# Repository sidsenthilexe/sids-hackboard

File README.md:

# Sid's Hackboard
My hackboard is pretty closely based on my current keyboard (Steelseries Apex 3 TKL) because it fits very well for what I need it to do. Probably could have optimized it more but ran out of time.                         
I'll probably make some keys macros especially the cluster around Delete.                   
It also includes a volume knob + a switch for play/pause, skip, and rewind.                         
This was actually way easier than hackpad because I now use KiCad and Fusion a lot more (even for other projects), but figuring out how to do the integrated plate was a bit annoying, and drafting the edges also took some figuring out.                      
Anyway I made a (hopefully) functional keyboard.                    

## Key Features:
* Standard TKL layout
* Plate with integrated case
* Magnetic lift bar - totally not copied from s76
* Volume knob
* Probably way too tall but I didn't bother to measure properly

## CAD/case:
M3 (M5? idek) bolts and heatset inserts are used to hold the 2 pieces together, and an integrated plate is used to hold the pcb.

## PCB:
A matrix is wired to prevent ghosting - the wiring took way too long. There are 84 total keys and one rotary encoder + switch, organized in 17 columns and 6 rows.

## Firmware:
KMK was used for the firmware, I still need to figure out how to implement the volume controls though.

## BOM:
|ITEM|QTY|PRICE|
|----|---|-----|
|Orpheus Pico|1|price|
|mx switches|qty|price|
|stabs|qty|price|
|encoder|qty|price|
|3x10x60mm Magnets|1 pack of 4|5.99|
|1N4148 diodes|qty|price|
|keycaps|qty|price|
|bolts|qty|price|
|heatset inserts|qty|price|

## Images:
Fully assembled:          
               
Schematic:          
                           
PCB:            
                                                   
Case:

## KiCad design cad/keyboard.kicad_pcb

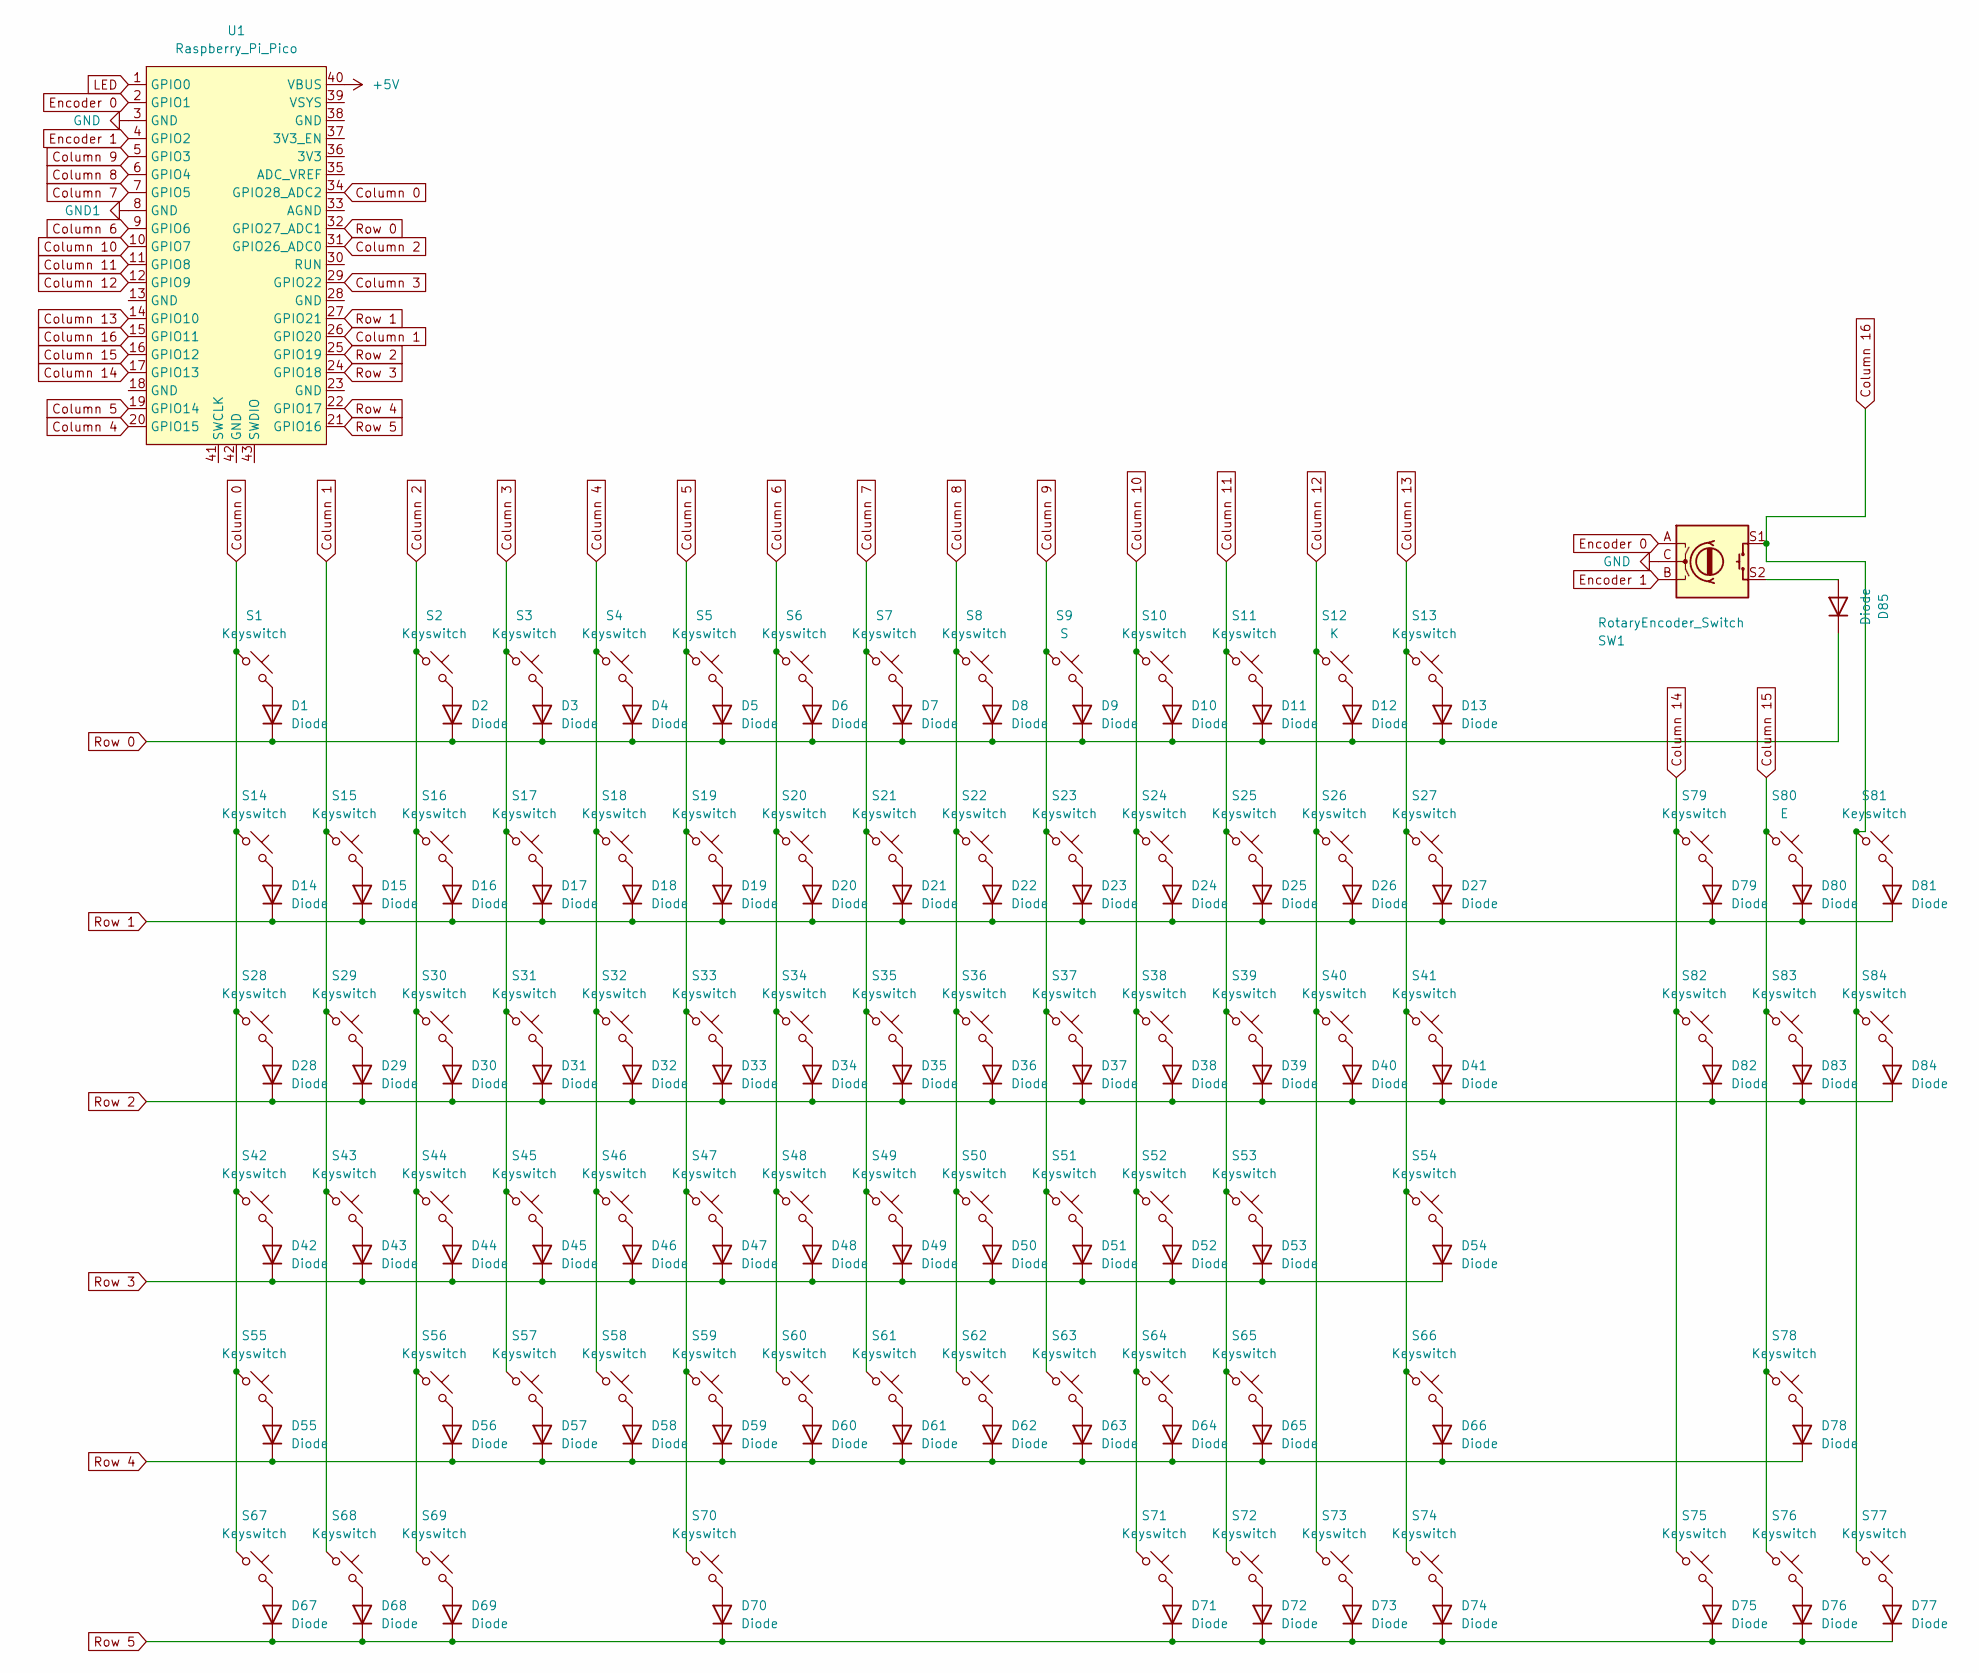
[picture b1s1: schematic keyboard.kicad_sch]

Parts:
D1, D2, D3, D4, D5, D6, D7, D8, D9, D10, D11, D12, D13, D14, D15, D16, D17, D18, D19, D20, D21, D22, D23, D24, D25, D26, D27, D28, D29, D30, D31, D32, D33, D34, D35, D36, D37, D38, D39, D40, D41, D42, D43, D44, D45, D46, D47, D48, D49, D50, D51, D52, D53, D54, D55, D56, D57, D58, D59, D60, D61, D62, D63, D64, D65, D66, D67, D68, D69, D70, D71, D72, D73, D74, D75, D76, D77, D78, D79, D80, D81, D82, D83, D84, D85: Diode; Diode_DO-35
S1, S2, S3, S4, S5, S6, S7, S8, S10, S11, S13, S14, S15, S16, S17, S18, S19, S20, S21, S22, S23, S24, S25, S26, S29, S30, S31, S32, S33, S34, S35, S36, S37, S38, S39, S40, S43, S44, S45, S46, S47, S48, S49, S50, S51, S52, S53, S56, S57, S58, S59, S60, S61, S62, S63, S64, S65, S75, S76, S77, S78, S79, S81, S82, S83, S84: Keyswitch; MX_PCB_1.00u
S9: S; MX_PCB_1.00u
S12: K; MX_PCB_1.00u
S27: Keyswitch; MX_PCB_2.00u
S28, S41: Keyswitch; MX_PCB_1.50u
S42: Keyswitch; MX_PCB_1.75u
S54, S55: Keyswitch; MX_PCB_2.25u
S66: Keyswitch; MX_PCB_2.75u
S67, S68, S69, S71, S72, S73, S74: Keyswitch; MX_PCB_1.25u
S70: Keyswitch; MX_PCB_6.25u
S80: E; MX_PCB_1.00u
SW1: RotaryEncoder_Switch; RotaryEncoder_Alps_EC11E-Switch_Vertical_H20mm
U1: Raspberry_Pi_Pico

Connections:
+5V: U1.40 (VBUS)
Column 0: S1.1, S14.1, S28.1, S42.1, S55.1, S67.1, U1.34 (GPIO28_ADC2)
Column 1: S15.1, S29.1, S43.1, S68.1, U1.26 (GPIO20)
Column 2: S2.1, S16.1, S30.1, S44.1, S56.1, S69.1, U1.31 (GPIO26_ADC0)
Column 3: S3.1, S17.1, S31.1, S45.1, S57.1, U1.29 (GPIO22)
Column 4: S4.1, S18.1, S32.1, S46.1, S58.1, U1.20 (GPIO15)
Column 5: S5.1, S19.1, S33.1, S47.1, S59.1, S70.1, U1.19 (GPIO14)
Column 6: S6.1, S20.1, S34.1, S48.1, S60.1, U1.9 (GPIO6)
Column 7: S7.1, S21.1, S35.1, S49.1, S61.1, U1.7 (GPIO5)
Column 8: S8.1, S22.1, S36.1, S50.1, S62.1, U1.6 (GPIO4)
Column 9: S9.1, S23.1, S37.1, S51.1, S63.1, U1.5 (GPIO3)
Column 10: S10.1, S24.1, S38.1, S52.1, S64.1, S71.1, U1.10 (GPIO7)
Column 11: S11.1, S25.1, S39.1, S53.1, S65.1, S72.1, U1.11 (GPIO8)
Column 12: S12.1, S26.1, S40.1, S73.1, U1.12 (GPIO9)
Column 13: S13.1, S27.1, S41.1, S54.1, S66.1, S74.1, U1.14 (GPIO10)
Column 14: S75.1, S79.1, S82.1, U1.17 (GPIO13)
Column 15: S76.1, S78.1, S80.1, S83.1, U1.16 (GPIO12)
Column 16: S77.1, S81.1, S84.1, SW1.S1, U1.15 (GPIO11)
Encoder 0: SW1.A, U1.2 (GPIO1)
Encoder 1: SW1.B, U1.4 (GPIO2)
GND: SW1.C, U1.3 (GND)
GND1: U1.8 (GND)
LED: U1.1 (GPIO0)
unnamed: D1.2 (A), S1.2
unnamed: D2.2 (A), S2.2
unnamed: D3.2 (A), S3.2
unnamed: D4.2 (A), S4.2
unnamed: D5.2 (A), S5.2
unnamed: D6.2 (A), S6.2
unnamed: D7.2 (A), S7.2
unnamed: D8.2 (A), S8.2
unnamed: D9.2 (A), S9.2
unnamed: D10.2 (A), S10.2
unnamed: D11.2 (A), S11.2
unnamed: D12.2 (A), S12.2
unnamed: D13.2 (A), S13.2
unnamed: D14.2 (A), S14.2
unnamed: D15.2 (A), S15.2
unnamed: D16.2 (A), S16.2
unnamed: D17.2 (A), S17.2
unnamed: D18.2 (A), S18.2
unnamed: D19.2 (A), S19.2
unnamed: D20.2 (A), S20.2
unnamed: D21.2 (A), S21.2
unnamed: D22.2 (A), S22.2
unnamed: D23.2 (A), S23.2
unnamed: D24.2 (A), S24.2
unnamed: D25.2 (A), S25.2
unnamed: D26.2 (A), S26.2
unnamed: D27.2 (A), S27.2
unnamed: D28.2 (A), S28.2
unnamed: D29.2 (A), S29.2
unnamed: D30.2 (A), S30.2
unnamed: D31.2 (A), S31.2
unnamed: D32.2 (A), S32.2
unnamed: D33.2 (A), S33.2
unnamed: D34.2 (A), S34.2
unnamed: D35.2 (A), S35.2
unnamed: D36.2 (A), S36.2
unnamed: D37.2 (A), S37.2
unnamed: D38.2 (A), S38.2
unnamed: D39.2 (A), S39.2
unnamed: D40.2 (A), S40.2
unnamed: D41.2 (A), S41.2
unnamed: D42.2 (A), S42.2
unnamed: D43.2 (A), S43.2
unnamed: D44.2 (A), S44.2
unnamed: D45.2 (A), S45.2
unnamed: D46.2 (A), S46.2
unnamed: D47.2 (A), S47.2
unnamed: D48.2 (A), S48.2
unnamed: D49.2 (A), S49.2
unnamed: D50.2 (A), S50.2
unnamed: D51.2 (A), S51.2
unnamed: D52.2 (A), S52.2
unnamed: D53.2 (A), S53.2
unnamed: D54.2 (A), S54.2
unnamed: D55.2 (A), S55.2
unnamed: D56.2 (A), S56.2
unnamed: D57.2 (A), S57.2
unnamed: D58.2 (A), S58.2
unnamed: D59.2 (A), S59.2
unnamed: D60.2 (A), S60.2
unnamed: D61.2 (A), S61.2
unnamed: D62.2 (A), S62.2
unnamed: D63.2 (A), S63.2
unnamed: D64.2 (A), S64.2
unnamed: D65.2 (A), S65.2
unnamed: D66.2 (A), S66.2
unnamed: D67.2 (A), S67.2
unnamed: D68.2 (A), S68.2
unnamed: D69.2 (A), S69.2
unnamed: D70.2 (A), S70.2
unnamed: D71.2 (A), S71.2
unnamed: D72.2 (A), S72.2
unnamed: D73.2 (A), S73.2
unnamed: D74.2 (A), S74.2
unnamed: D75.2 (A), S75.2
unnamed: D76.2 (A), S76.2
unnamed: D77.2 (A), S77.2
unnamed: D78.2 (A), S78.2
unnamed: D79.2 (A), S79.2
unnamed: D80.2 (A), S80.2
unnamed: D81.2 (A), S81.2
unnamed: D82.2 (A), S82.2
unnamed: D83.2 (A), S83.2
unnamed: D84.2 (A), S84.2
unnamed: D85.2 (A), SW1.S2
Row 0: D1.1 (K), D2.1 (K), D3.1 (K), D4.1 (K), D5.1 (K), D6.1 (K), D7.1 (K), D8.1 (K), D9.1 (K), D10.1 (K), D11.1 (K), D12.1 (K), D13.1 (K), D85.1 (K), U1.32 (GPIO27_ADC1)
Row 1: D14.1 (K), D15.1 (K), D16.1 (K), D17.1 (K), D18.1 (K), D19.1 (K), D20.1 (K), D21.1 (K), D22.1 (K), D23.1 (K), D24.1 (K), D25.1 (K), D26.1 (K), D27.1 (K), D79.1 (K), D80.1 (K), D81.1 (K), U1.27 (GPIO21)
Row 2: D28.1 (K), D29.1 (K), D30.1 (K), D31.1 (K), D32.1 (K), D33.1 (K), D34.1 (K), D35.1 (K), D36.1 (K), D37.1 (K), D38.1 (K), D39.1 (K), D40.1 (K), D41.1 (K), D82.1 (K), D83.1 (K), D84.1 (K), U1.25 (GPIO19)
Row 3: D42.1 (K), D43.1 (K), D44.1 (K), D45.1 (K), D46.1 (K), D47.1 (K), D48.1 (K), D49.1 (K), D50.1 (K), D51.1 (K), D52.1 (K), D53.1 (K), D54.1 (K), U1.24 (GPIO18)
Row 4: D55.1 (K), D56.1 (K), D57.1 (K), D58.1 (K), D59.1 (K), D60.1 (K), D61.1 (K), D62.1 (K), D63.1 (K), D64.1 (K), D65.1 (K), D66.1 (K), D78.1 (K), U1.22 (GPIO17)
Row 5: D67.1 (K), D68.1 (K), D69.1 (K), D70.1 (K), D71.1 (K), D72.1 (K), D73.1 (K), D74.1 (K), D75.1 (K), D76.1 (K), D77.1 (K), U1.21 (GPIO16)

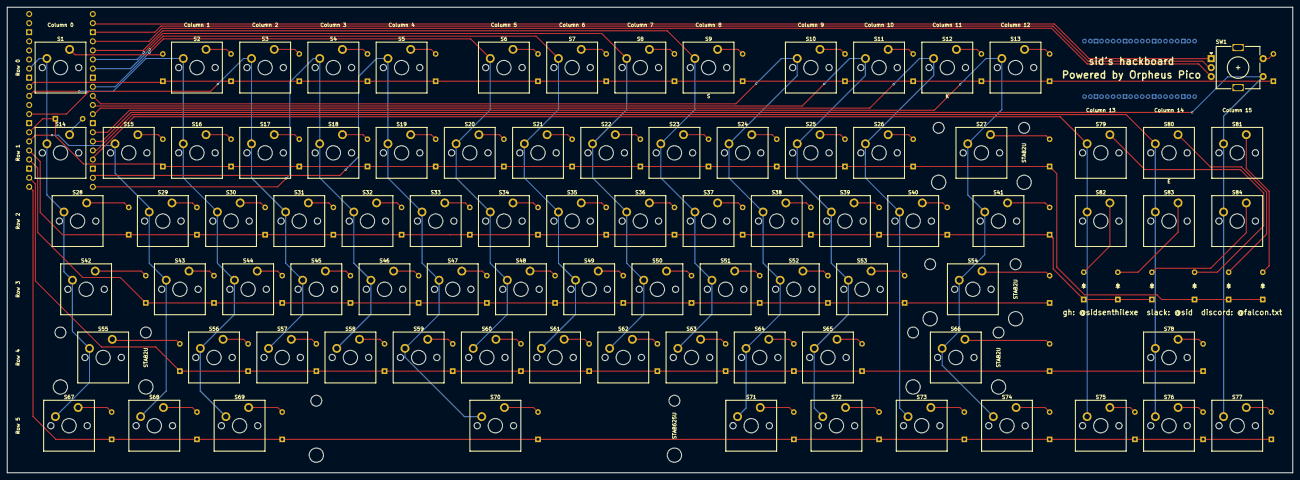
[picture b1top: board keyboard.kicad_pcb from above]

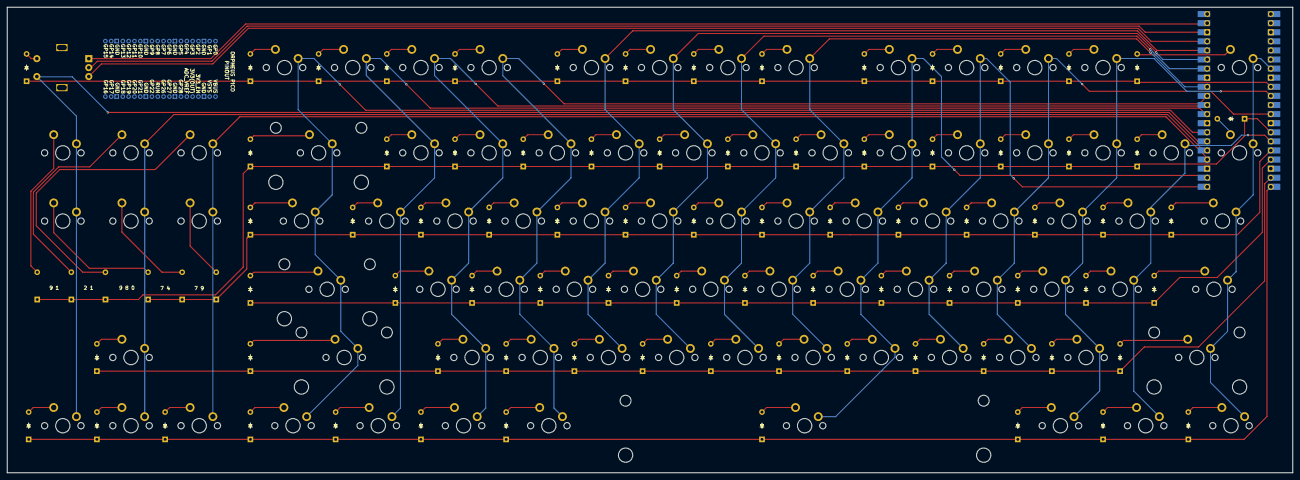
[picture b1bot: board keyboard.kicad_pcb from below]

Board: 2 copper layers, 359.0 x 130.0 mm, 176 parts (80 on the bottom side), 111 nets.

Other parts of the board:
STAB2U, STAB2U#2, STAB2U#3, STAB2U#4: Stabilizer_MX_2.00u
STAB625U: Stabilizer_MX_6.25u

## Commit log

2025-03-20 Update everything
2025-03-20 fix names
